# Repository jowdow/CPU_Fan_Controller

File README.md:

<div id="top"></div>

<!-- PROJECT SHIELDS -->
<!--
*** I'm using markdown "reference style" links for readability.
*** Reference links are enclosed in brackets [ ] instead of parentheses ( ).
*** See the bottom of this document for the declaration of the reference variables
*** for contributors-url, forks-url, etc. This is an optional, concise syntax you may use.
*** https://www.markdownguide.org/basic-syntax/#reference-style-links
-->
[![MIT License][license-shield]][license-url]
[![LinkedIn][linkedin-shield]][linkedin-url]

<!-- PROJECT LOGO -->
<br />
<div align="center">
  
<h3 align="center">CPU Fan Controller</h3>

  <p align="center">
    Minimal adjustable speed fan controller with USB-C PD
    <br />
    <a href="https://youtu.be/27ypUMn-c7k">View Demo</a>
  </p>
</div>

<!-- TABLE OF CONTENTS -->
<details>
  <summary>Table of Contents</summary>
  <ol>
    <li>
      <a href="#about-the-project">About The Project</a>
      <ul>
        <li><a href="#built-with">Built With</a></li>
      </ul>
    </li>
    <li>
      <a href="#getting-started">Getting Started</a>
      <ul>
        <li><a href="#prerequisites">Prerequisites</a></li>
        <li><a href="#installation">Installation</a></li>
      </ul>
    </li>
    <li><a href="#usage">Usage</a></li>
    <li><a href="#roadmap">Roadmap</a></li>
    <li><a href="#license">License</a></li>
    <li><a href="#contact">Contact</a></li>
    <li><a href="#acknowledgments">Acknowledgments</a></li>
  </ol>
</details>

<!-- ABOUT THE PROJECT -->
## About The Project

This is a PWM-based CPU fan speed controller using a potentiometer, a button, and USB-C PD to function. Once the button is pressed it starts the fan at a speed that is set by the value the potentiometer is at.

<p align="right">(<a href="#top">back to top</a>)</p>

### Built With

* [STM32CubeIDE](https://www.python.org/)

<p align="right">(<a href="#top">back to top</a>)</p>

<!-- GETTING STARTED -->
## Getting Started

FILLER

### Prerequisites

#### WOAH
FILLER

### Installation

FILLER

<!-- USAGE EXAMPLES -->
## Usage

<!--Use this space to show useful examples of how a project can be used. Additional screenshots, code examples and demos work well in this space. You may also link to more resources. -->

FILLER 

### Normal Operation

FILLER [link](https://youtu.be/27ypUMn-c7k) 

<p align="right">(<a href="#top">back to top</a>)</p>

<!-- ROADMAP -->
## Roadmap
### (Here for future)

- [Create an enclosure]
- [Programming Apparatus] 

<p align="right">(<a href="#top">back to top</a>)</p>

<!-- Troublt Shooting -->
## Trouble Shooting
FILLER

<!-- LICENSE -->
## License
 FILLER

<p align="right">(<a href="#top">back to top</a>)</p>

<!-- CONTACT -->
## Contact

Joseph Douglas - [@jowdow2](https://twitter.com/jowdow2) - jdougla16@rockets.utoledo

Project Link: [https://github.com/jowdow/CPU_FanController](https://github.com/jowdow/CPU_FanController)

<p align="right">(<a href="#top">back to top</a>)</p>

<!-- MARKDOWN LINKS & IMAGES -->
<!-- All of these need to be updated -->
<!-- https://www.markdownguide.org/basic-syntax/#reference-style-links -->

[license-shield]: https://img.shields.io/github/license/jowdow/DeliveryArmCapstone.svg?style=for-the-badge
[license-url]: https://github.com/jowdow/DeliveryArmCapstone/blob/master/LICENSE.txt
[linkedin-shield]: https://img.shields.io/badge/-linkedin-black.svg?style=for-the-badge&logo=linkedin&colorB=555
[linkedin-url]: https://www.linkedin.com/in/joseph-douglas937/

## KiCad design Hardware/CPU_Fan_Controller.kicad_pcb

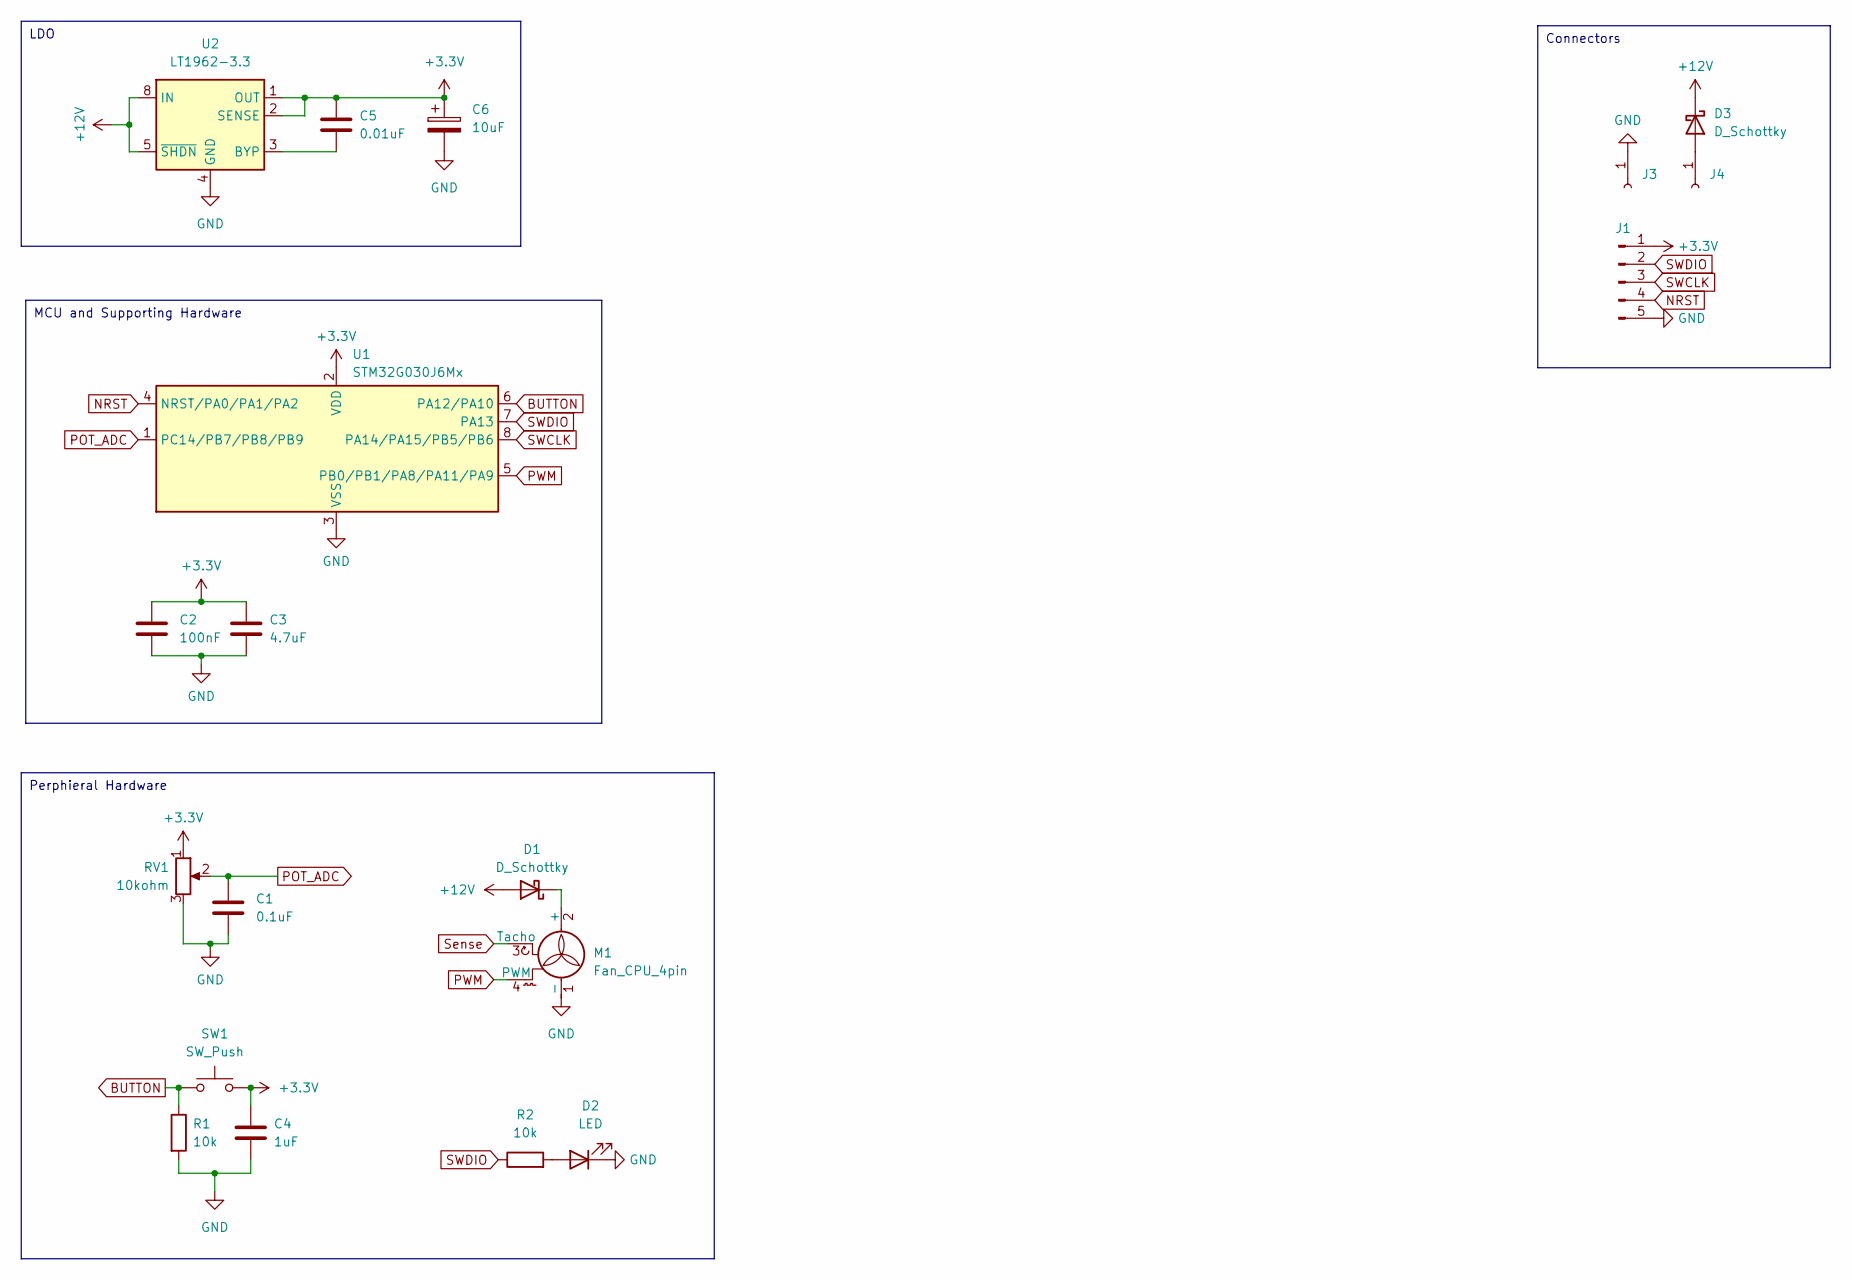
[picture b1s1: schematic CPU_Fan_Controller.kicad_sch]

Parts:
C1: 0.1uF; C_0603_1608Metric
C2: 100nF; C_0603_1608Metric
C3: 4.7uF; C_0603_1608Metric
C4: 1uF; C_0603_1608Metric_Pad1.08x0.95mm_HandSolder
C5: 0.01uF; C_0603_1608Metric_Pad1.08x0.95mm_HandSolder
C6: 10uF; CP_EIA-6032-15_Kemet-U
D1, D3: D_Schottky; D_0805_2012Metric_Pad1.15x1.40mm_HandSolder
D2: LED; LED_0603_1608Metric
J1: Conn_01x05_Pin; PinHeader_1x05_P2.54mm_Vertical
J3, J4: Conn_01x01_Socket; Pin_D1.0mm_L10.0mm
M1: Fan_CPU_4pin; PinHeader_1x04_P2.54mm_Horizontal
R1, R2: 10k; R_0603_1608Metric_Pad0.98x0.95mm_HandSolder
RV1: 10kohm; Potentiometer_Bourns_3299W_Vertical
SW1: SW_Push; SW_SPST_B3SL-1002P
U1: STM32G030J6Mx; SOIC-8_3.9x4.9mm_P1.27mm
U2: LT1962-3.3; MSOP-8_3x3mm_P0.65mm

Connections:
+3.3V: C2.1, C3.1, C4.1, C5.2, C6.1, J1.1, RV1.1, SW1.2, U1.2 (VDD), U2.1 (OUT), U2.2 (SENSE)
+12V: D1.2 (A), D3.1 (K), U2.5 (~SHDN), U2.8 (IN)
BUTTON: R1.1, SW1.1, U1.6 (PA12/PA10)
GND: C1.2, C2.2, C3.2, C4.2, C6.2, D2.1 (K), J1.5, J3.1, M1.1 (-), R1.2, RV1.3, U1.3 (VSS), U2.4 (GND)
NRST: J1.4, U1.4 (NRST/PA0/PA1/PA2)
unnamed: D1.1 (K), M1.2 (+)
unnamed: D2.2 (A), R2.2
unnamed: D3.2 (A), J4.1
unnamed: C5.1, U2.3 (BYP)
POT_ADC: C1.1, RV1.2, U1.1 (PC14/PB7/PB8/PB9)
PWM: M1.4 (PWM), U1.5 (PB0/PB1/PA8/PA11/PA9)
SWCLK: J1.3, U1.8 (PA14/PA15/PB5/PB6)
SWDIO: J1.2, R2.1, U1.7 (PA13)
Sense: M1.3 (Tacho)

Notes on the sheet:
Connectors
Perphieral Hardware
MCU and Supporting Hardware
LDO

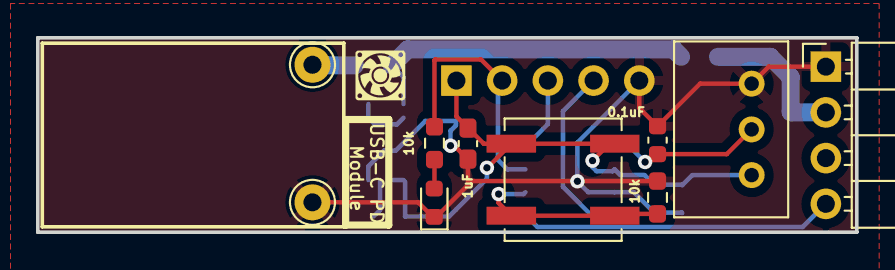
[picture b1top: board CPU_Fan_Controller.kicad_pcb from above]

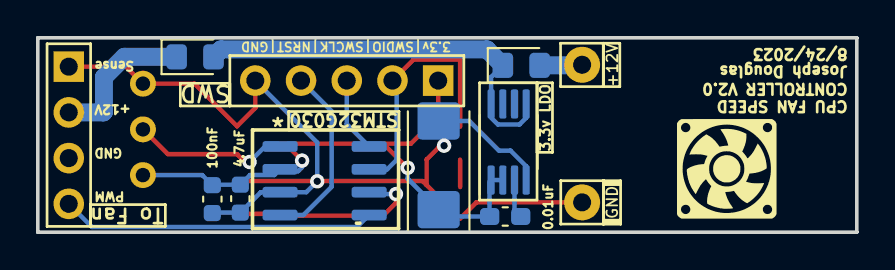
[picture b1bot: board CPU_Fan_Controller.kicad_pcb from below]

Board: 2 copper layers, 45.5 x 10.8 mm, 19 parts (8 on the bottom side), 13 nets.

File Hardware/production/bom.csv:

Designator,Footprint,Quantity,Value,LCSC Part #
C1,0603,1,0.1uF,
C2,0603,1,100nF,
C3,0603,1,4.7uF,
C4,0603,1,1uF,
C5,0603,1,0.01uF,
C6,CP_EIA-6032-15_Kemet-U,1,10uF,
"D1, D3",0805,2,D_Schottky,
D2,0603,1,LED,
J1,PinHeader_1x05_P2.54mm_Vertical,1,Conn_01x05_Pin,
"J3, J4",Pin_D1.0mm_L10.0mm,2,Conn_01x01_Socket,
M1,PinHeader_1x04_P2.54mm_Horizontal,1,Fan_CPU_4pin,
"R1, R2",0603,2,10k,
RV1,Potentiometer_Bourns_3299W_Vertical,1,10kohm,
SW1,SW_SPST_B3SL-1002P,1,SW_Push,
U1,SOIC-8_3.9x4.9mm_P1.27mm,1,STM32G030J6Mx,
U2,MSOP-8_3x3mm_P0.65mm,1,LT1962-3.3,

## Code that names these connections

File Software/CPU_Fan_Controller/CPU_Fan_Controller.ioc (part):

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Mcu.Name=STM32G030J6Mx
Mcu.Package=SO8N
Mcu.UserName=STM32G030J6Mx
PA12\ [PA10].GPIOParameters=GPIO_PuPd,GPIO_Label
PA12\ [PA10].GPIO_Label=Button_Input
PA12\ [PA10].GPIO_PuPd=GPIO_PULLDOWN
PA12\ [PA10].Signal=GPXTI12
PA14-BOOT0__PA15__PB5__PB6.StandardMode=true
PA8.GPIOParameters=GPIO_Label
PA8.GPIO_Label=Fan_PWM
PA8.Signal=S_TIM1_CH1
PB0__PB1__PA8__PA11\ [PA9].StandardMode=true
PB7.GPIOParameters=GPIO_Label
PB7.GPIO_Label=Potentiometer
PB7.Mode=IN11
PB7.Signal=ADC1_IN11
PC14-OSC32_IN\ (PC14)__PB7__PB8__PB9.StandardMode=true
RCC.HSE_VALUE=8000000
RCC.SYSCLKFreq_VALUE=16000000
board=custom

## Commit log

2023-08-19 Init commit
2023-08-31 Code is functioning, updated PCB
2023-08-31 Adding Pictures
